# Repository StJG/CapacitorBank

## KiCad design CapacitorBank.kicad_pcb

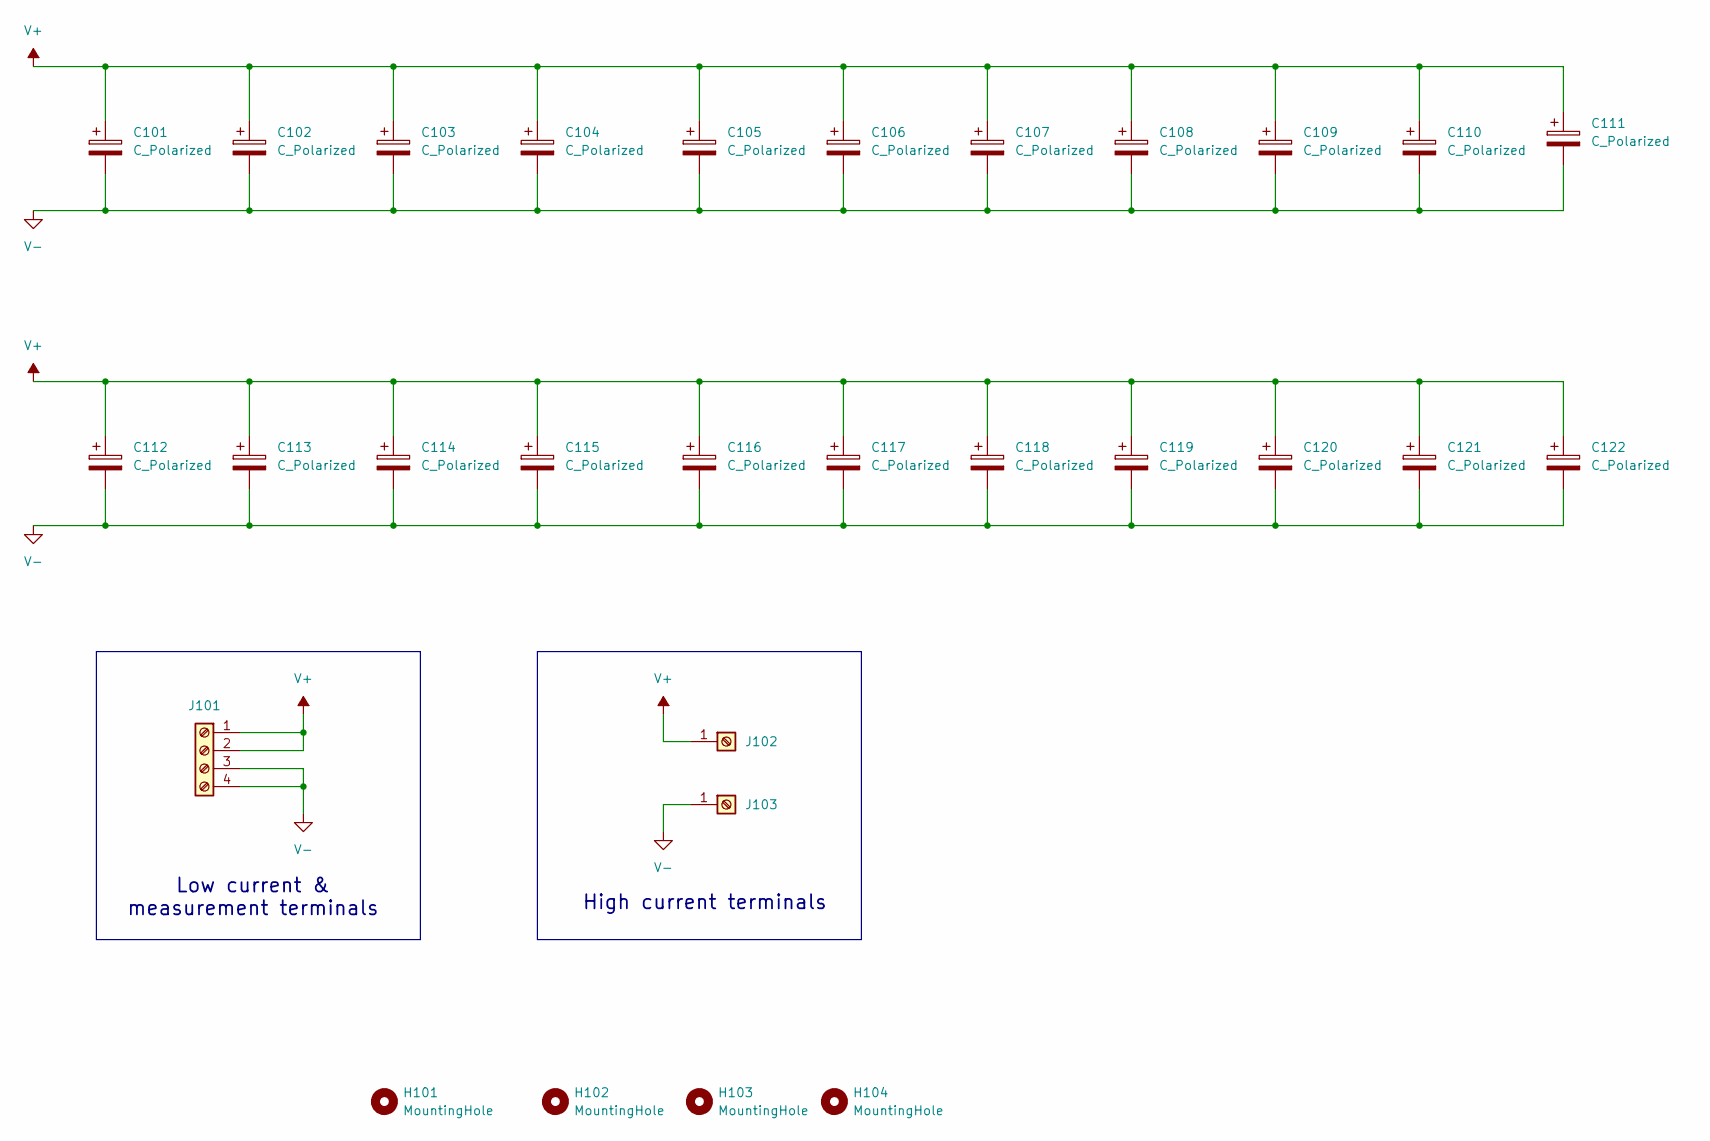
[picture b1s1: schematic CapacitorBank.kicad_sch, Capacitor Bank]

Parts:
C101, C102, C103, C104, C105, C106, C107, C108, C109, C110, C111, C112, C113, C114, C115, C116, C117, C118, C119, C120, C121, C122: C_Polarized; CP_Radial_D18.0mm_P7.50mm
H101, H102, H103, H104: MountingHole; MountingHole_3.2mm_M3
J101: Screw_Terminal_01x04; TerminalBlock_Phoenix_MKDS-1,5-4-5.08_1x04_P5.08mm_Horizont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
J102, J103: Screw_Terminal_01x01; Wuerth_REDCUBE-THR_WP-THRSH_74651175_THR

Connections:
V+: C101.1, C102.1, C103.1, C104.1, C105.1, C106.1, C107.1, C108.1, C109.1, C110.1, C111.1, C112.1, C113.1, C114.1, C115.1, C116.1, C117.1, C118.1, C119.1, C120.1, C121.1, C122.1, J101.1, J101.2, J102.1
V-: C101.2, C102.2, C103.2, C104.2, C105.2, C106.2, C107.2, C108.2, C109.2, C110.2, C111.2, C112.2, C113.2, C114.2, C115.2, C116.2, C117.2, C118.2, C119.2, C120.2, C121.2, C122.2, J101.3, J101.4, J103.1

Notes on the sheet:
Low current & measurement terminals
High current terminals

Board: 2 copper layers, 29 parts (0 on the bottom side), 2 nets, no tracks yet.
